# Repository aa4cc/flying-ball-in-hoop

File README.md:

Check out our new [webpage](https://aa4cc.github.io/flying-ball-in-hoop/) to find out more about our Ball and Hoop model.

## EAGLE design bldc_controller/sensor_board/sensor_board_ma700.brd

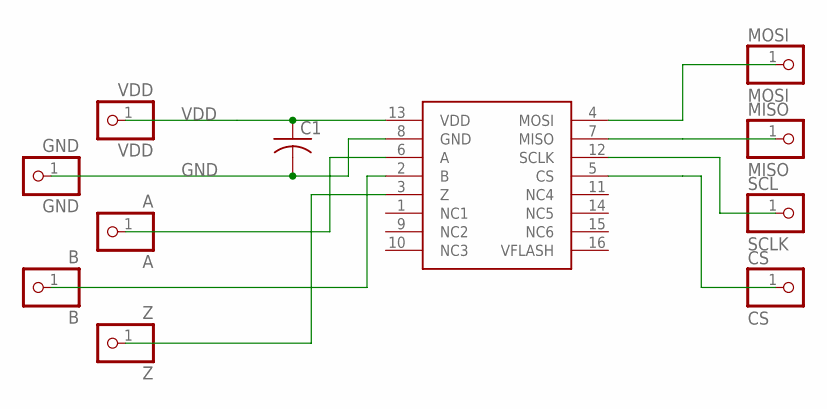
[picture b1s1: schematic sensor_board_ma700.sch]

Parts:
A: A; 1X01
B: B; 1X01
C1: C-USC0603; C0603
CS: CS; 1X01
GND: GND; 1X01
MA700: MA700; QFN16
MISO: MISO; 1X01
MOSI: MOSI; 1X01
SCL: SCLK; 1X01
VDD: VDD; 1X01
Z: Z; 1X01

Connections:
GND: C1.2, GND.1, MA700.8 (GND)
unnamed: B.1, MA700.2 (B)
unnamed: CS.1, MA700.5 (CS)
unnamed: A.1, MA700.6 (A)
unnamed: MA700.3 (Z), Z.1
unnamed: MA700.7 (MISO), MISO.1
unnamed: MA700.12 (SCLK), SCL.1
unnamed: MA700.4 (MOSI), MOSI.1
VDD: C1.1, MA700.13 (VDD), VDD.1

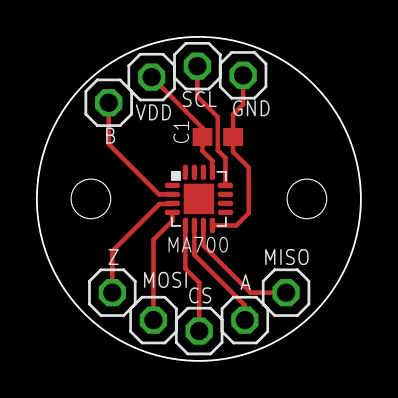
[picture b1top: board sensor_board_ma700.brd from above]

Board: 2 copper layers, 18.0 x 18.0 mm, 11 parts (0 on the bottom side), 9 nets.

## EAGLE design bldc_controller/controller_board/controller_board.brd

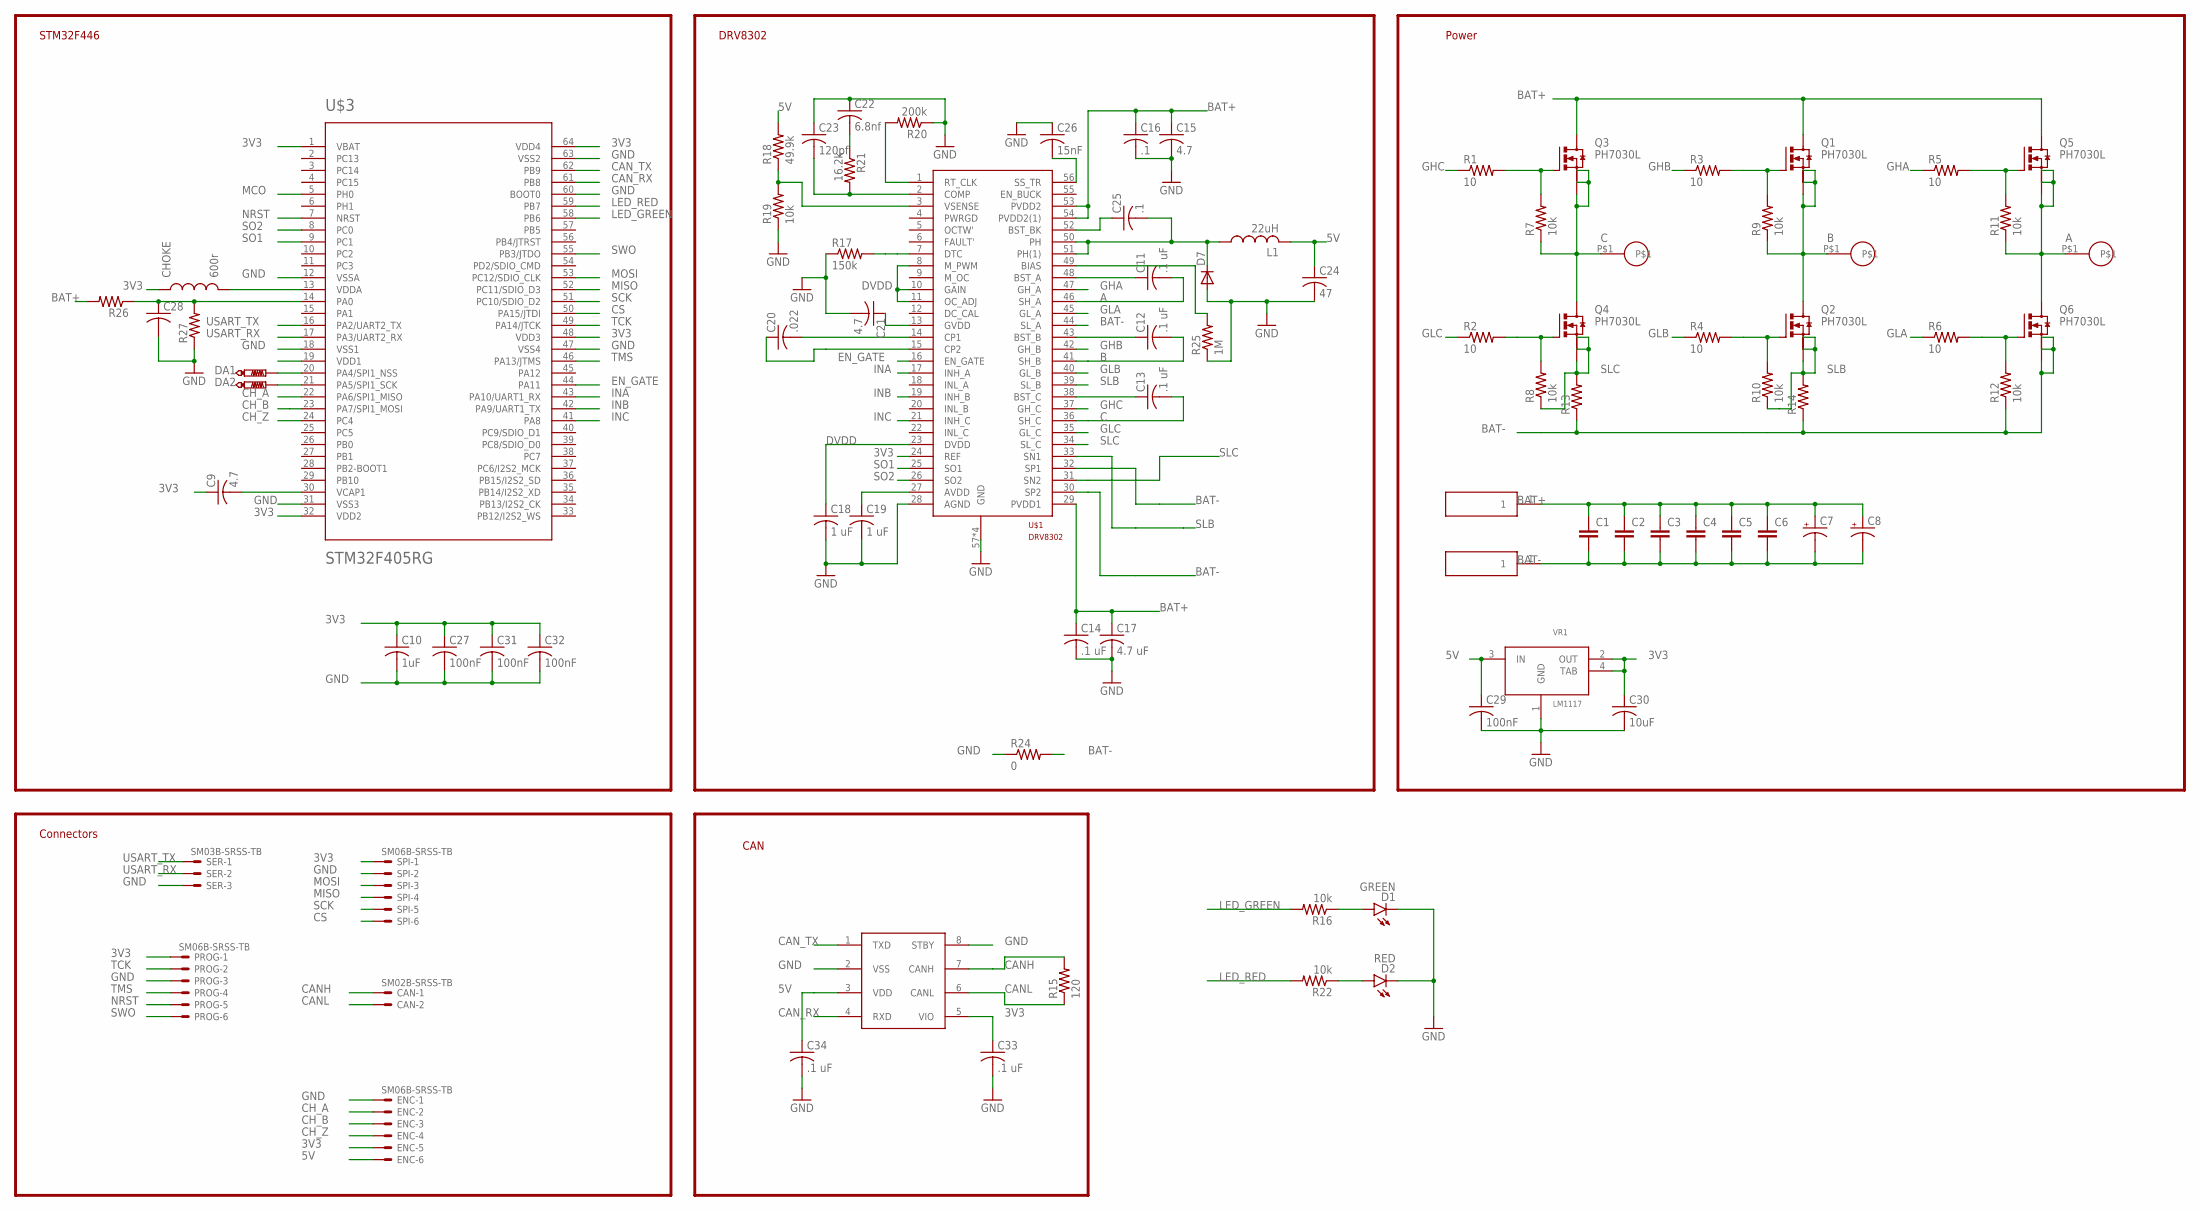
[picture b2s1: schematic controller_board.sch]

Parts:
C1, C2, C3, C4, C5, C6: C-EUC0805; C0805
C7, C8: CPOL-USE3.5-8; E3,5-8
C9: 4.7; C0603
C10: 1uF; C0603
C11, C12, C13, C14: .1 uF; C0603
C15, C21: 4.7; C0805
C16, C25: .1; C0603
C17: 4.7 uF; C0805
C18, C19: 1 uF; C0603
C20: .022; C0603
C22: 6.8nf; C0603
C23: 120pf; C0603
C24: 47; C1210
C26: 15nF; C0603
C27, C29, C31, C32: 100nF; C0603
C28: C-USC0603; C0603
C30: 10uF; C0603
C33, C34: .1 uF; C0603K
CAN: SM02B-SRSS-TB
CHOKE: 600r; 0603
D1: GREEN; LED-0603
D2: RED; LED-0603
D7: DIODE-DO-214AC; DO-214AC
DA1, DA2: PTR1TP12R; TP12R
ENC: SM06B-SRSS-TB
J4, J5: 0.125_PAD
L1: 22uH; L4532P
PROG: SM06B-SRSS-TB
Q1, Q2, Q3, Q4, Q5, Q6: PH7030L; SOT669
R1, R2, R3, R4, R5, R6: 10; R0603
R7, R8, R9, R10, R11, R12, R16, R19, R22: 10k; R0603
R13, R14: R-US_R1210; R1210
R15: 120; R0603
R17: 150k; R0603
R18: 49.9k; R0603
R20: 200k; R0603
R21: 16.2k; R0603
R24: 0; R0603
R25: 1M; R0603
R26, R27: R-US_R0603; R0603
SER: SM03B-SRSS-TB
SPI: SM06B-SRSS-TB
U$1: DRV8302; HTSSOP56
U$2, U$4, U$5: 18_AWG_PAD
U$3: STM32F405RG; TQFP64
U$6: MCP2561; SO08
VR1: LM1117; SOT-223

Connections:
3V3: C9.1, C10.1, C27.1, C30.1, C31.1, C32.1, C33.1, CHOKE.1, ENC.5, PROG.1, SPI.1, U$1.24 (REF), U$3.1 (VBAT), U$3.19 (VDD1), U$3.32 (VDD2), U$3.48 (VDD3), U$3.64 (VDD4), U$6.5 (VIO), VR1.2 (OUT), VR1.4 (TAB)
5V: C24.1, C29.1, C34.1, ENC.6, L1.2, R18.2, U$6.3 (VDD), VR1.3 (IN)
A: C11.2, Q5.1 (S), Q5.2 (S), Q5.3 (S), Q6.MB (D), R11.1, U$1.46 (SH_A), U$5.P$1
B: C12.2, Q1.1 (S), Q1.2 (S), Q1.3 (S), Q2.MB (D), R9.1, U$1.41 (SH_B), U$4.P$1
BAT+: C1.1, C2.1, C3.1, C4.1, C5.1, C6.1, C7.+, C8.+, C14.1, C15.1, C16.1, C17.1, J4.1, Q1.MB (D), Q3.MB (D), Q5.MB (D), R26.2, U$1.29 (PVDD1), U$1.53 (PVDD2), U$1.54 (PVDD2(1))
BAT-: C1.2, C2.2, C3.2, C4.2, C5.2, C6.2, C7.-, C8.-, J5.1, Q6.1 (S), Q6.2 (S), Q6.3 (S), R12.1, R13.1, R14.1, R24.2, U$1.30 (SP2), U$1.32 (SP1), U$1.44 (SL_A)
C: C13.2, Q3.1 (S), Q3.2 (S), Q3.3 (S), Q4.MB (D), R7.1, U$1.36 (SH_C), U$2.P$1
CANH: CAN.1, R15.2, U$6.7 (CANH)
CANL: CAN.2, R15.1, U$6.6 (CANL)
CAN_RX: U$3.61 (PB8), U$6.4 (RXD)
CAN_TX: U$3.62 (PB9), U$6.1 (TXD)
CH_A: ENC.2, U$3.22 (PA6/SPI1_MISO)
CH_B: ENC.3, U$3.23 (PA7/SPI1_MOSI)
CH_Z: ENC.4, U$3.24 (PC4)
CS: SPI.6, U$3.50 (PA15/JTDI)
DVDD: C18.1, U$1.8 (M_PWM), U$1.10 (GAIN), U$1.11 (OC_ADJ), U$1.23 (DVDD)
EN_GATE: U$1.16 (EN_GATE), U$3.44 (PA11)
GHA: R5.1, U$1.47 (GH_A)
GHB: R3.1, U$1.42 (GH_B)
GHC: R1.1, U$1.37 (GH_C)
GLA: R6.1, U$1.45 (GL_A)
GLB: R4.1, U$1.40 (GL_B)
GLC: R2.1, U$1.35 (GL_C)
GND: C10.2, C14.2, C15.2, C16.2, C17.2, C18.2, C19.2, C21.2, C22.1, C23.1, C24.2, C26.1, C27.2, C28.2, C29.2, C30.2, C31.2, C32.2, C33.2, C34.2, D1.C, D2.C, D7.A, ENC.1, PROG.3, R17.1, R19.1, R20.1, R24.1, R25.1, R27.1, SER.3, SPI.2, U$1.28 (AGND), U$1.57 (GND), U$1.P$1 (GND), U$1.P$2 (GND), U$1.P$3 (GND), U$3.12 (VSSA), U$3.18 (VSS1), U$3.31 (VSS3), U$3.47 (VSS4), U$3.60 (BOOT0), U$3.63 (VSS2), U$6.2 (VSS), U$6.8 (STBY), VR1.1 (GND)
INA: U$1.17 (INH_A), U$3.43 (PA10/UART1_RX)
INB: U$1.19 (INH_B), U$3.42 (PA9/UART1_TX)
INC: U$1.21 (INH_C), U$3.41 (PA8)
LED_GREEN: R16.2, U$3.58 (PB6)
LED_RED: R22.2, U$3.59 (PB7)
MCO: U$3.5 (PH0)
MISO: SPI.4, U$3.52 (PC11/SDIO_D3)
MOSI: SPI.3, U$3.53 (PC12/SDIO_CLK)
unnamed: Q3.4 (G), R1.2, R7.2
unnamed: CHOKE.2, U$3.13 (VDDA)
unnamed: C9.2, U$3.30 (VCAP1)
unnamed: C11.1, U$1.48 (BST_A)
unnamed: R25.2, U$1.49 (BIAS)
unnamed: C13.1, U$1.38 (BST_C)
unnamed: Q4.4 (G), R2.2, R8.2
unnamed: Q1.4 (G), R3.2, R9.2
unnamed: C12.1, U$1.43 (BST_B)
unnamed: Q5.4 (G), R5.2, R11.2
unnamed: Q6.4 (G), R6.2, R12.2
unnamed: R18.1, R19.2, U$1.3 (VSENSE)
unnamed: R17.2, U$1.7 (DTC)
unnamed: C19.1, U$1.27 (AVDD)
unnamed: C20.2, U$1.14 (CP1)
unnamed: C20.1, U$1.15 (CP2)
unnamed: C21.1, U$1.13 (GVDD)
unnamed: C23.2, R21.2, U$1.2 (COMP)
unnamed: R20.2, U$1.1 (RT_CLK)
unnamed: C22.2, R21.1
unnamed: C25.2, D7.C, L1.1, U$1.50 (PH), U$1.51 (PH(1))
unnamed: C25.1, U$1.52 (BST_BK)
unnamed: C26.2, U$1.56 (SS_TR)
unnamed: C28.1, R26.1, R27.2, U$3.14 (PA0)
unnamed: D1.A, R16.1
unnamed: Q2.4 (G), R4.2, R10.2
unnamed: D2.A, R22.1
unnamed: DA1.TP, U$3.20 (PA4/SPI1_NSS)
unnamed: DA2.TP, U$3.21 (PA5/SPI1_SCK)
NRST: PROG.5, U$3.7 (NRST)
SCK: SPI.5, U$3.51 (PC10/SDIO_D2)
SLB: Q2.1 (S), Q2.2 (S), Q2.3 (S), R10.1, R14.2, U$1.33 (SN1), U$1.39 (SL_B)
SLC: Q4.1 (S), Q4.2 (S), Q4.3 (S), R8.1, R13.2, U$1.31 (SN2), U$1.34 (SL_C)
SO1: U$1.25 (SO1), U$3.9 (PC1)
SO2: U$1.26 (SO2), U$3.8 (PC0)
SWO: PROG.6, U$3.55 (PB3/JTDO)
TCK: PROG.2, U$3.49 (PA14/JTCK)
TMS: PROG.4, U$3.46 (PA13/JTMS)
USART_RX: SER.2, U$3.17 (PA3/UART2_RX)
USART_TX: SER.1, U$3.16 (PA2/UART2_TX)

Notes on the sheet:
DRV8302
STM32F446
Connectors
Power
CAN

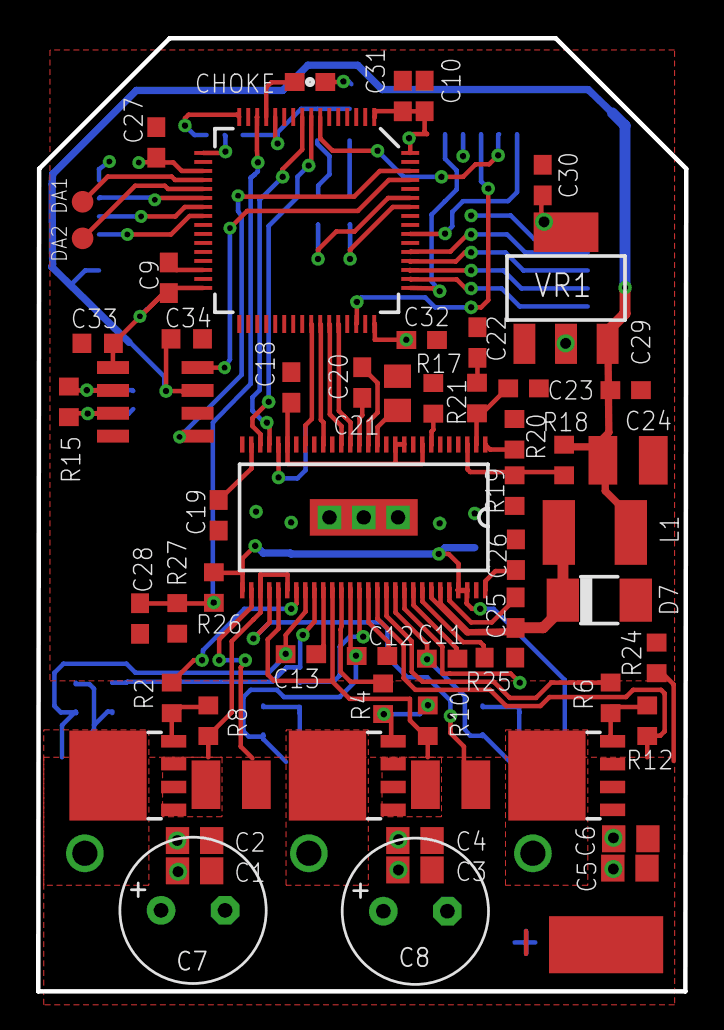
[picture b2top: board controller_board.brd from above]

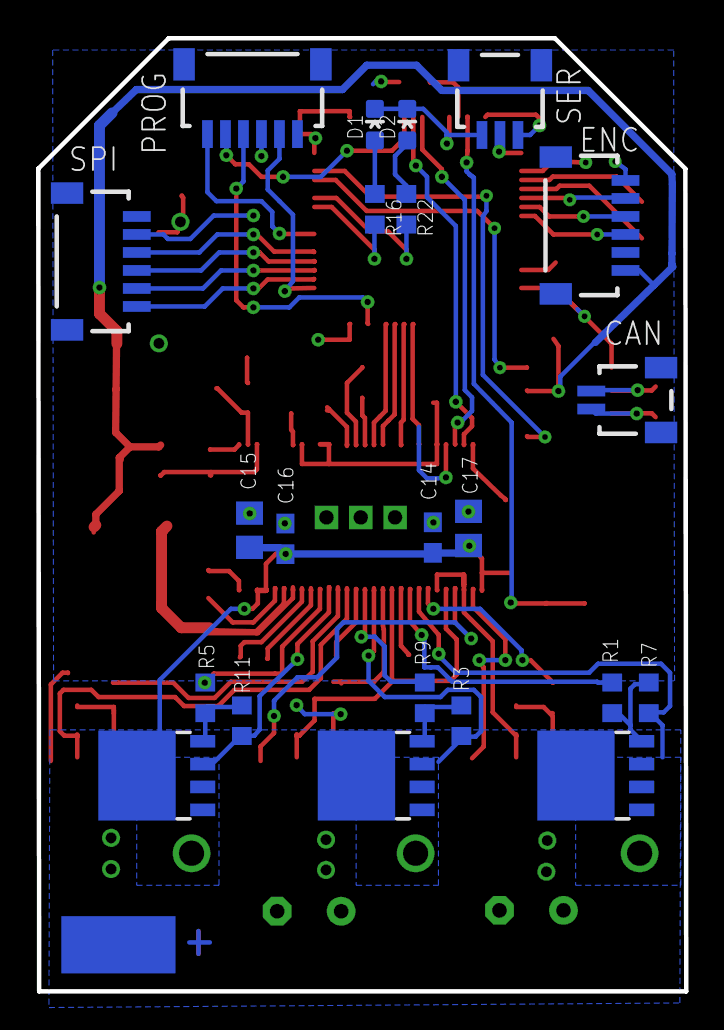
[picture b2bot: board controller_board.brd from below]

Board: 2 copper layers, 36.0 x 52.9 mm, 87 parts (23 on the bottom side), 71 nets.

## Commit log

2016-11-13 init
2016-11-13 README.md added
2017-06-14 doc folder added
2018-09-26 raspi-ballpos module added
2018-09-27 Shutdown button service added
2018-09-27 README updated
2018-09-27 Experimental web page added
2018-09-27 Web template added
2018-09-27 First verision of the webpages
2018-09-27 Some minor details regarding the web pages changed
2018-09-29 Building instruction divided to HW and SW parts
2018-10-01 Raspicam-lamp repository added as a submodule
2018-10-01 favicon added
2018-10-01 asdf
2018-10-05 black backsheet added
2018-10-10 new content uploaded
2018-10-10 formatting changes
2018-10-12 Future development added
2018-10-12 Formatting
2018-10-12 More pictures
2018-10-12 Submodules updated
2018-10-15 README modified to reflect the fact that all information is presented on the new webpage.
2018-10-15 index.md subtitle added
2018-10-15 index.md modified
2018-10-15 power-off script modified so that it lits up the power LED
2018-10-15 shtdown script updated
2018-10-15 scheme moved
2018-10-17 new box photos
2018-10-17 new photos
2018-10-31 index.md introupdated
2019-01-02 raspiballpos updated
2019-01-02 jekyl web template updated
2019-01-02 raspiball updated
2019-01-29 gemfile security issue resolved
2019-02-22 Laser Cutter
2019-08-22 Bump nokogiri from 1.8.5 to 1.10.4 in /docs
    Bumps [nokogiri](https://github.com/sparklemotion/nokogiri) from 1.8.5 to 1.10.4.
    - [Release notes](https://github.com/sparklemotion/nokogiri/releases)
    - [Changelog](https://github.com/sparklemotion/nokogiri/blob/master/CHANGELOG.md)
    - [Commits](https://github.com/sparklemotion/nokogiri/compare/v1.8.5...v1.10.4)
2020-02-25 Bump rubyzip from 1.2.2 to 2.2.0 in /docs
    Bumps [rubyzip](https://github.com/rubyzip/rubyzip) from 1.2.2 to 2.2.0.
    - [Release notes](https://github.com/rubyzip/rubyzip/releases)
    - [Changelog](https://github.com/rubyzip/rubyzip/blob/master/Changelog.md)
    - [Commits](https://github.com/rubyzip/rubyzip/compare/v1.2.2...v2.2.0)
2020-02-25 Bump nokogiri from 1.10.4 to 1.10.8 in /docs
    Bumps [nokogiri](https://github.com/sparklemotion/nokogiri) from 1.10.4 to 1.10.8.
    - [Release notes](https://github.com/sparklemotion/nokogiri/releases)
    - [Changelog](https://github.com/sparklemotion/nokogiri/blob/master/CHANGELOG.md)
    - [Commits](https://github.com/sparklemotion/nokogiri/compare/v1.10.4...v1.10.8)
2021-05-19 Bump nokogiri from 1.10.8 to 1.11.4 in /docs
    Bumps [nokogiri](https://github.com/sparklemotion/nokogiri) from 1.10.8 to 1.11.4.
    - [Release notes](https://github.com/sparklemotion/nokogiri/releases)
    - [Changelog](https://github.com/sparklemotion/nokogiri/blob/main/CHANGELOG.md)
    - [Commits](https://github.com/sparklemotion/nokogiri/compare/v1.10.8...v1.11.4)

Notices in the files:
parts and their libraries:
SparkFun-Passives: Licensing: Creative Commons ShareAlike 4.0 International - https://creativecommons.org/licenses/by-sa/4.0
